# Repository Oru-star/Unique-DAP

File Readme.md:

# Unique DAP

Unique DAP is an ESP32-S3-based portable audio player built around a dedicated high-performance audio DAC and headphone amplifier. It uses a Sharp reflective memory display rather than a conventional backlit LCD, removable microSD storage, and two rotary encoders for navigation. Charging is provided through a USB Type-C port.

## Project at a glance

- **Controller:** Espressif ESP32-S3 module
- **Audio:** ESS ES9038Q2M DAC and MAX97220A headphone amplifier
- **Display:** Sharp LS032B7DD02, 3.16-inch reflective memory LCD
- **Storage:** Removable microSDXC card; 128 GB target capacity
- **Controls:** Two rotary encoders and tactile/slide controls (final switch variants still under verification)
- **Design files:** KiCad schematic and PCB, Gerbers, and printable enclosure parts

## Repository contents

| Resource | Description |
|---|---|
| [KiCad PCB](<DAP'S PCB/DAP'S PCB.kicad_pcb>) | Main board layout |
| [KiCad schematic](<DAP'S PCB/DAP'S PCB.kicad_sch>) | Main circuit schematic |
| [Gerber files](<DAP'S PCB/Gerbers/>) | PCB manufacturing outputs |
| [Printable enclosure parts](<steps/Stl for prints/>) | 3D-printable enclosure parts |
| [Full BOM with INR/USD prices and links](./Bom.csv) | Complete component register with supplier links, manufacturer references, price class and engineering notes |

## Project images

### Enclosure

<p align="center"><em>Top view</em></p>

<p align="center"><em>Front side view</em></p>

### PCB

<p align="center"><em>PCB top view</em></p>

<p align="center"><em>PCB side view</em></p>

## Bill of materials

**The complete BOM is [`Bom.csv`](./Bom.csv).** It includes all 38 BOM entries, MPNs/candidates, manufacturer references, purchase links, INR/USD unit prices, extended prices, price classification and engineering notes.

- **BOM lines with numeric prices or budget allowances:** 38 of 38
- **Budgetary estimates (not supplier quotes):** 4
- **Lines still requiring a quote:** 0
- **Current priced/estimated subtotal:** ₹12,892.44 / $137.32
- **FX reference:** 1 USD = ₹93.8516

> **Pricing caveat:** The subtotal includes supplier/list-price references and clearly marked budgetary estimates. It is not a final landed cost. Reconfirm all prices, stock, taxes, shipping, customs and reeling fees at checkout. PCB fabrication, assembly, stencil and tools are excluded.

### Detailed component pricing and purchase links

Links below were refreshed. Direct manufacturer/distributor product pages are used where available; otherwise the link opens an exact-MPN supplier search. Search results do not guarantee stock or orderability.

| Category | RefDes | Qty | Manufacturer / MPN | Manufacturer reference | Purchase link | Unit INR | Unit USD | Extended INR | Extended USD | Price class | Design status |
|---|---|---:|---|---|---|---:|---:|---:|---:|---|---|
| Display | DISP1 | 1 | `LS032B7DD02` | [Manufacturer / datasheet](https://global.sharp/products/device/lineup/selection/lcd/mobile/index.html) | [Supplier / lookup](https://www.digikey.in/en/products/detail/sharp-microelectronics/LS032B7DD02/23349498) | ₹3,739.83 | $39.85 | ₹3,739.83 | $39.85 | PRICE REFERENCE — reconfirm checkout | VERIFY |
| DAC | IC1 | 1 | `ES9038Q2M` | [Manufacturer / datasheet](https://www.mouser.in/en/ProductDetail/ESS-Technology/ES9038Q2M?qs=sPbYRqrBIVmdeUedURuuOw%3D%3D) | [Supplier / lookup](https://www.mouser.in/en/ProductDetail/ESS-Technology/ES9038Q2M?qs=sPbYRqrBIVmdeUedURuuOw%3D%3D) | ₹1,967.96 | $20.97 | ₹1,967.96 | $20.97 | PRICE REFERENCE — reconfirm checkout | BUY |
| Power IC | U1 | 1 | `TPS61023DRLR` | [Manufacturer / datasheet](https://www.ti.com/product/TPS61023/part-details/TPS61023DRLR) | [Supplier / lookup](https://www.digikey.in/en/products/detail/texas-instruments/TPS61023DRLR/11310667) | ₹116.56 | $1.24 | ₹116.56 | $1.24 | PRICE REFERENCE — reconfirm checkout | BUY |
| Power IC | U2 | 1 | `TPS63021DSJR` | [Manufacturer / datasheet](https://www.ti.com/product/TPS63021/part-details/TPS63021DSJR) | [Supplier / lookup](https://www.digikey.in/en/products/detail/texas-instruments/TPS63021DSJR/2271632) | ₹384.11 | $4.09 | ₹384.11 | $4.09 | PRICE REFERENCE — reconfirm checkout | BUY |
| Charger IC | U3 | 1 | `BQ25895RTWR` | [Manufacturer / datasheet](https://www.ti.com/product/BQ25895) | [Supplier / lookup](https://www.digikey.in/en/products/detail/texas-instruments/BQ25895RTWR/5214018) | ₹321.05 | $3.42 | ₹321.05 | $3.42 | PRICE REFERENCE — reconfirm checkout | VERIFY |
| USB-C controller | U4 | 1 | `TUSB320LAIRWBR` | [Manufacturer / datasheet](https://www.ti.com/product/TUSB320LAI/part-details/TUSB320LAIRWBR) | [Supplier / lookup](https://www.digikey.in/en/products/detail/texas-instruments/TUSB320LAIRWBR/5722618) | ₹174.05 | $1.85 | ₹174.05 | $1.85 | PRICE REFERENCE — reconfirm checkout | BUY |
| Headphone amplifier | U5 | 1 | `MAX97220AETE+T` | [Manufacturer / datasheet](https://www.analog.com/en/products/max97220a.html) | [Supplier / lookup](https://www.digikey.in/en/products/detail/analog-devices-inc-maxim-integrated/MAX97220AETE-T/2744332) | ₹245.56 | $2.62 | ₹245.56 | $2.62 | PRICE REFERENCE — reconfirm checkout | BUY |
| MCU module | U6 | 1 | `ESP32-S3-WROOM-1-N8R8` | [Manufacturer / datasheet](https://www.espressif.com/en/products/modules/esp32-s3-wroom-1) | [Supplier / lookup](https://www.digikey.in/en/products/detail/espressif-systems/ESP32-S3-WROOM-1-N8R8/16705630) | ₹603.88 | $6.43 | ₹603.88 | $6.43 | PRICE REFERENCE — reconfirm checkout | VERIFY |
| USB-C receptacle | J1 | 1 | `USB4105-GF-A` | [Manufacturer / datasheet](https://gct.co/connector/usb4105) | [Supplier / lookup](https://www.digikey.in/en/products/detail/gct/USB4105-GF-A/11198510) | ₹76.44 | $0.81 | ₹76.44 | $0.81 | PRICE REFERENCE — reconfirm checkout | VERIFY |
| Battery header | J2 | 1 | `TSW-102-07-G-S` | [Manufacturer / datasheet](https://www.samtec.com/products/tsw-102-07-g-s) | [Supplier / lookup](https://www.digikey.in/en/products/detail/samtec-inc/TSW-102-07-G-S/1101325) | ₹20.07 | $0.21 | ₹20.07 | $0.21 | PRICE REFERENCE — reconfirm checkout | VERIFY |
| Programming header | J3 | 1 | `TSW-105-07-G-S` | [Manufacturer / datasheet](https://www.samtec.com/products/tsw-105-07-g-s) | [Supplier / lookup](https://www.digikey.in/en/products/detail/samtec-inc/TSW-105-07-G-S/1101322) | ₹40.66 | $0.43 | ₹40.66 | $0.43 | PRICE REFERENCE — reconfirm checkout | BUY |
| Display FPC connector | J4 | 1 | `FH34SRJ-10S-0.5SH(50)` | [Manufacturer / datasheet](https://www.hirose.com/en/product/p/CL0580-1251-5-50) | [Supplier / lookup](https://www.digikey.in/en/products/detail/hirose-electric-co-ltd/FH34SRJ-10S-0-5SH-50/3880296) | ₹116.57 | $1.24 | ₹116.57 | $1.24 | PRICE REFERENCE — reconfirm checkout | VERIFY |
| Headphone jack | J5 | 1 | `SJ1-3533NG` | [Manufacturer / datasheet](https://www.digikey.in/en/products/detail/same-sky-formerly-cui-devices/SJ1-3533NG/738701) | [Supplier / lookup](https://www.digikey.in/en/products/detail/same-sky-formerly-cui-devices/SJ1-3533NG/738701) | ₹160.74 | $1.71 | ₹160.74 | $1.71 | PRICE REFERENCE — reconfirm checkout | BUY |
| Ferrite bead | FB1 | 1 | `BLM21PG601SN1D` | [Manufacturer / datasheet](https://www.murata.com/en-global/products/productdetail?partno=BLM21PG601SN1D) | [Supplier / lookup](https://www.digikey.in/en/products/detail/murata-electronics/BLM21PG601SN1D/24763118) | ₹11.47 | $0.12 | ₹11.47 | $0.12 | PRICE REFERENCE — reconfirm checkout | VERIFY |
| Power inductor | L1 | 1 | `74438357010` | [Manufacturer / datasheet](https://www.we-online.com/en/components/products/WE-MAPI) | [Supplier / lookup](https://in.element14.com/wurth-elektronik/74438357010/inductor-1uh-7-4a-20-shielded/dp/2842181) | ₹161.46 | $1.72 | ₹161.46 | $1.72 | PRICE REFERENCE — reconfirm checkout | HOLD |
| Power inductor | L2 | 1 | `XFL4020-152ME` | [Manufacturer / datasheet](https://www.coilcraft.com/en-us/products/power/high-voltage-inductors/xfl/xfl4020/) | [Supplier / lookup](https://www.coilcraft.com/en-us/products/power/high-voltage-inductors/xfl/xfl4020/) | ₹231.81 | $2.47 | ₹231.81 | $2.47 | LIST PRICE REFERENCE — confirm configuration | HOLD |
| Power inductor | L3 | 1 | `DFE322512F-2R2M=P2` | [Manufacturer / datasheet](https://www.murata.com/en-global/products/productdetail?partno=DFE322512F-2R2M%3DP2) | [Supplier / lookup](https://www.digikey.in/en/products/detail/murata-electronics/DFE322512F-2R2M-P2/9815914) | ₹46.82 | $0.50 | ₹46.82 | $0.50 | PRICE REFERENCE — reconfirm checkout | HOLD |
| Oscillator | Y1 | 1 | `ASE-40.000MHZ-L-C-T` | [Manufacturer / datasheet](https://abracon.com/Oscillators/ASE.pdf) | [Supplier / lookup](https://www.digikey.in/en/products/detail/abracon-llc/ASE-40-000MHZ-L-C-T/5980161) | ₹99.37 | $1.06 | ₹99.37 | $1.06 | PRICE REFERENCE — reconfirm checkout | VERIFY |
| Capacitor | C1,C8-C10,C13,C14,C30 | 7 | `CL10A106KP8NNND` | [Manufacturer / datasheet](https://www.samsungsem.com/global/product/passive-component/mlcc.do) | [Supplier / lookup](https://www.digikey.in/en/products/detail/samsung-electro-mechanics/CL10A106KP8NNND/3894249) | ₹19.11 | $0.20 | ₹133.77 | $1.43 | PRICE REFERENCE — reconfirm checkout | VERIFY |
| Capacitor | C2,C16-C21,C23,C28,C31 | 10 | `GRM188R71H104KA93D` | [Manufacturer / datasheet](https://www.murata.com/en-global/products/productdetail?partno=GRM188R71H104KA93D) | [Supplier / lookup](https://www.digikey.in/en/products/detail/murata-electronics/GRM188R71H104KA93D/587143) | ₹15.29 | $0.16 | ₹152.90 | $1.63 | PRICE REFERENCE — reconfirm checkout | VERIFY |
| Capacitor | C3-C6 | 4 | `CC0603MRX5R5BB226` | [Manufacturer / datasheet](https://www.yageo.com/en/ProductSearch/Index) | [Supplier / lookup](https://www.digikey.in/en/products/detail/yageo/CC0603MRX5R5BB226/5195222) | ₹54.46 | $0.58 | ₹217.84 | $2.32 | PRICE REFERENCE — reconfirm checkout | HOLD |
| Capacitor | C7,C12,C24-C27,C29,C32,C34,C35 | 10 | `C1608X7R1C105K080AC` | [Manufacturer / datasheet](https://product.tdk.com/en/search/capacitor/ceramic/mlcc/info?part_no=C1608X7R1C105K080AC) | [Supplier / lookup](https://www.digikey.in/en/products/result?keywords=C1608X7R1C105K080AC) | ₹11.47 | $0.12 | ₹114.70 | $1.22 | PRICE REFERENCE — reconfirm checkout | VERIFY |
| Capacitor | C15,C22,C36-C39 | 6 | `GRM188R71A475KE15D` | [Manufacturer / datasheet](https://www.murata.com/en-global/products/productdetail?partno=GRM188R71A475KE15D) | [Supplier / lookup](https://www.digikey.in/en/products/result?keywords=GRM188R71A475KE15D) | ₹5.00 | $0.05 | ₹30.00 | $0.32 | ESTIMATE — not a supplier quote | VERIFY |
| Capacitor | C11 | 1 | `GRM188R71E473KA61D` | [Manufacturer / datasheet](https://www.murata.com/en-global/products/productdetail?partno=GRM188R71E473KA61D) | [Supplier / lookup](https://www.digikey.in/en/products/result?keywords=GRM188R71E473KA61D) | ₹3.00 | $0.03 | ₹3.00 | $0.03 | ESTIMATE — not a supplier quote | VERIFY |
| Capacitor | C33 | 1 | `GRM1885C1H561JA01D` | [Manufacturer / datasheet](https://www.murata.com/en-global/products/productdetail?partno=GRM1885C1H561JA01D) | [Supplier / lookup](https://www.digikey.in/en/products/detail/murata-electronics/GRM1885C1H561JA01D/586954) | ₹15.29 | $0.16 | ₹15.29 | $0.16 | PRICE REFERENCE — reconfirm checkout | VERIFY |
| Resistor | R4,R6,R7,R9-R11,R15,R16,R18,R19,R27 | 11 | `RC0805FR-0710KL` | [Manufacturer / datasheet](https://www.yageo.com/en/ProductSearch/Index) | [Supplier / lookup](https://www.digikey.in/en/products/detail/yageo/RC0805FR-0710KL/730482) | ₹3.25 | $0.03 | ₹35.74 | $0.38 | PRICE REFERENCE — reconfirm checkout | BUY |
| Resistor | R17,R20-R26 | 8 | `CRG0805F20K` | [Manufacturer / datasheet](https://www.te.com/en/product-1622825-1.html) | [Supplier / lookup](https://www.digikey.in/en/products/detail/te-connectivity-passive-product/CRG0805F20K/2380867) | ₹9.51 | $0.10 | ₹76.08 | $0.81 | PRICE REFERENCE — reconfirm checkout | BUY |
| Resistor | R5,R8 | 2 | `RC0805FR-07260RL` | [Manufacturer / datasheet](https://www.yageo.com/en/ProductSearch/Index) | [Supplier / lookup](https://www.digikey.in/en/products/result?keywords=RC0805FR-07260RL) | ₹3.00 | $0.03 | ₹6.00 | $0.06 | ESTIMATE — not a supplier quote | VERIFY |
| Resistor | R13,R14 | 2 | `RC0805FR-074K7L` | [Manufacturer / datasheet](https://www.yageo.com/en/ProductSearch/Index) | [Supplier / lookup](https://www.digikey.in/en/products/detail/yageo/RC0805FR-074K7L/727929) | ₹9.56 | $0.10 | ₹19.12 | $0.20 | PRICE REFERENCE — reconfirm checkout | VERIFY |
| Resistor | R1 | 1 | `RC0805FR-07100KL` | [Manufacturer / datasheet](https://www.yageo.com/en/ProductSearch/Index) | [Supplier / lookup](https://www.digikey.in/en/products/detail/yageo/RC0805FR-07100KL/730491) | ₹10.51 | $0.11 | ₹10.51 | $0.11 | PRICE REFERENCE — reconfirm checkout | VERIFY |
| Resistor | R2 | 1 | `RC0805FR-0727K4L` | [Manufacturer / datasheet](https://www.yageo.com/en/ProductSearch/Index) | [Supplier / lookup](https://www.digikey.in/en/products/detail/yageo/RC0805FR-0727K4L/727782) | ₹9.56 | $0.10 | ₹9.56 | $0.10 | PRICE REFERENCE — reconfirm checkout | VERIFY |
| Resistor | R3 | 1 | `RC0805FR-07200KL` | [Manufacturer / datasheet](https://www.yageo.com/en/ProductSearch/Index) | [Supplier / lookup](https://www.digikey.in/en/products/detail/yageo/RC0805FR-07200KL/730671) | ₹9.56 | $0.10 | ₹9.56 | $0.10 | PRICE REFERENCE — reconfirm checkout | VERIFY |
| Resistor | R12 | 1 | `RC0805FR-07900KL` | [Manufacturer / datasheet](https://www.yageo.com/en/ProductSearch/Index) | [Supplier / lookup](https://www.digikey.in/en/products/result?keywords=RC0805FR-07900KL) | ₹3.00 | $0.03 | ₹3.00 | $0.03 | ESTIMATE — not a supplier quote | VERIFY |
| Rotary encoder | SW2,SW3 | 2 | `EC11E family — EC11E15204A3 price candidate` | [Manufacturer / datasheet](https://tech.alpsalpine.com/e/products/category/enc/) | [Supplier / lookup](https://www.digikey.in/en/products/detail/alps-alpine/EC11E15204A3/21721644) | ₹421.38 | $4.49 | ₹842.76 | $8.98 | PRICE REFERENCE — reconfirm checkout | HOLD |
| Slide / push controls | SW1,SW2-BOOT1,SW4-SW6 | 5 | `CHS-01A` | [Manufacturer / datasheet](https://www.nidec.com/en/product/search/category/B102/M101/S100/) | [Supplier / lookup](https://www.tanotis.com/products/nidec-copal-electronics-chs-01a-dip-switch-1pos-spst-slide-smd) | ₹169.20 | $1.80 | ₹846.00 | $9.01 | PRICE REFERENCE — reconfirm checkout | HOLD |
| Battery (off-board) | BAT1 (not a PCB footprint) | 1 | `WLY104050 — exact supplier/lead configuration TBD` | [Manufacturer / datasheet](https://robu.in/product-category/single-cell-micro-lipo-battery/) | [Supplier / lookup](https://robu.in/product-category/single-cell-micro-lipo-battery/) | ₹600.00 | $6.39 | ₹600.00 | $6.39 | INDIA LISTING — reconfirm checkout | HOLD |
| microSD card socket | J6 | 1 | `DM3AT-SF-PEJM5` | [Manufacturer / datasheet](https://www.hirose.com/product/document?clcode=CL0609-0031-0-00&documenttype=Drawing&lang=en) | [Supplier / lookup](https://www.digikey.in/en/products/detail/hirose-electric-co-ltd/DM3AT-SF-PEJM5/2533565) | ₹339.20 | $3.61 | ₹339.20 | $3.61 | PRICE REFERENCE — reconfirm checkout | VERIFY |
| Storage media | SD1 (off-board) | 1 | `SDSQUAB-128G-GN6MN` | [Manufacturer / datasheet](https://www.westerndigital.com/products/memory-cards/sandisk-ultra-uhs-i-microsd) | [Supplier / lookup](https://indiastore-stage.westerndigital.com/store/sdsquab-128g-gn6mn.html) | ₹909.00 | $9.69 | ₹909.00 | $9.69 | PRICE REFERENCE — reconfirm checkout | VERIFY |

### Link verification note

Direct DigiKey and Mouser product pages were substituted for several generic or stale search links. For parts without a confirmed exact product page, the purchase link opens a supplier search for the exact MPN; verify the result and suffix before ordering.

## Engineering review — unresolved approvals

**A numeric price, supplier link or footprint match does not constitute engineering approval.** The following checks remain mandatory before fabrication:

- **Power inductors L1/L2/L3:** Match each inductor to the actual converter topology, switching frequency, inductance range, peak and RMS current, saturation criterion, DCR loss, thermal rise, footprint and layout. For L2, the Coilcraft XFL4020 1.5 µH series data gives 15.8 mΩ maximum DCR, 4.1 A Isat at 10% inductance drop and 6.7 A Irms at 20°C rise. Compare against the calculated worst-case peak current, not just the converter's headline output current.
- **Battery BAT1:** Robu lists WLY104050 3.7 V, 2500 mAh at ₹600. This is a price reference only. Obtain the cell datasheet and verify dimensions, protection PCM, maximum charge voltage/current, continuous discharge current, NTC/temperature-sense requirements, lead connector and polarity. Keep HOLD until these are confirmed.
- **Battery connector J2:** Samtec TSW-102 is an unpolarized header. Prefer a keyed, locking connector matched to the battery harness; verify polarity and contact current. Do not approve an unkeyed battery connector without a deliberate safety review.
- **Capacitors C15,C22,C36-C39:** The ₹5/pc allowance for the 4.7 µF Murata candidate is a budget estimate, not a quote. Verify exact MPN and lifecycle, voltage rating, dielectric and effective capacitance at the actual DC bias.
- **Capacitor C11:** The ₹3/pc allowance for the 47 nF candidate is a budget estimate. Verify exact MPN, voltage rating, dielectric, tolerance and package against the circuit requirement.
- **Resistors R5/R8:** The ₹3/pc allowance is a budget estimate. Exact Yageo MPN RC0805FR-07260RL was not confirmed in distributor search. Verify the intended 260 Ω value and exact orderable code.
- **Resistor R12:** The ₹3/pc allowance is a budget estimate. Exact Yageo MPN RC0805FR-07900KL was not confirmed. Verify that 900 kΩ is intentional and confirm the exact orderable code; do not silently change it to 909 kΩ or 910 kΩ.
- **Oscillator Y1:** Confirm the 40 MHz oscillator against ES9038Q2M MCLK requirements and the full 44.1 kHz / 48 kHz audio clock plan before ordering.
- **Rotary encoders SW2/SW3:** EC11E15204A3 is a candidate without a push switch. Select a correct push-switch variant or add separate tact switches.
- **Control switches:** Copal CHS-01A is a slide switch, not a momentary pushbutton. Resolve symbol, footprint and actual user-interface function.
- **Capacitors C3-C6:** 22 µF, 6.3 V, 0603 MLCCs need effective-capacitance/DC-bias derating checks, especially on a 5 V rail.
- **Capacitor C2 group:** Confirm lifecycle status of the proposed 100 nF Murata part and choose an active replacement if obsolete.
- **Display DISP1:** Verify Sharp LS032B7DD02 full power rails, logic levels, FPC pinout, flex thickness and contact orientation against the exact panel documentation.
- **microSD J6:** Verify Hirose DM3AT-SF-PEJM5 pad mapping, shield pads and mechanical dimensions against the manufacturer drawing. Card-detect contacts may remain unconnected if unused.
- **USB-C J1:** Verify receptacle footprint, shell stakes, CC configuration, VBUS path, ESD protection and port role against the intended charge/data architecture.

## Assembly and bring-up

1. **Prepare parts:** Check exact MPN, package, footprint, pinout, ratings, lifecycle and availability. Do not substitute solely on nominal value.
2. **Review fabrication outputs:** Inspect the schematic, PCB, design-rule results, drill files, copper, solder mask, silkscreen and board outline. Independently inspect Gerbers before ordering.
3. **Inspect the bare PCB:** Check board damage, opens, shorts, solder-mask defects, drill sizes and connector alignment.
4. **Populate the PCB:** Use the assembly drawing and BOM. Apply solder paste with a stencil, place SMD parts, reflow to an appropriate profile, then install through-hole parts. Inspect fine-pitch ICs and connectors under magnification.
5. **Unpowered checks:** Measure resistance from every power rail to ground, verify polarity, inspect for solder bridges and confirm connector pin mapping.
6. **First power-up:** Use a current-limited bench supply rather than the Li-Po battery. Verify regulator outputs, startup sequencing, ripple, current draw and thermal behaviour before connecting the battery.
7. **Install display:** Confirm Sharp LS032B7DD02 flex orientation, pinout and supply rails. Never hot-plug the FPC.
8. **Install storage:** Use a compatible 128 GB microSDXC card. Firmware must support the selected filesystem; many 128 GB cards ship exFAT-formatted.
9. **Connect battery:** Only after battery polarity, protection, charger configuration, charge current and temperature sensing are verified against the cell datasheet.
10. **Functional validation:** Test display refresh, encoder direction/debounce, buttons, microSD read/write, USB-C operation, audio sample rates, headphone output and thermal performance.

## Firmware and storage notes

- The ESP32-S3 firmware must initialize the display, controls, microSD interface, audio pipeline, DAC and headphone amplifier.
- A 128 GB microSDXC card is commonly supplied as exFAT. Firmware must include compatible filesystem support or a documented reformat procedure.
- The microSD card is removable music/data storage; do not claim it is pre-flashed with firmware unless a specific image and flashing procedure are supplied. ESP32-S3 boot firmware normally resides in module flash.

## Project status

This is an actively developed hardware project. Prices and links are procurement references, not guarantees of stock, compatibility or production readiness. Electrical performance, power integrity, audio performance, thermal behaviour and enclosure fit require validation on the assembled hardware.

**Fabrication status: NOT APPROVED by this README/BOM alone.** Resolve all HOLD/VERIFY items, complete schematic and PCB review, and validate the Gerbers before ordering.

## License

Add the project license and any required third-party hardware/documentation attribution.

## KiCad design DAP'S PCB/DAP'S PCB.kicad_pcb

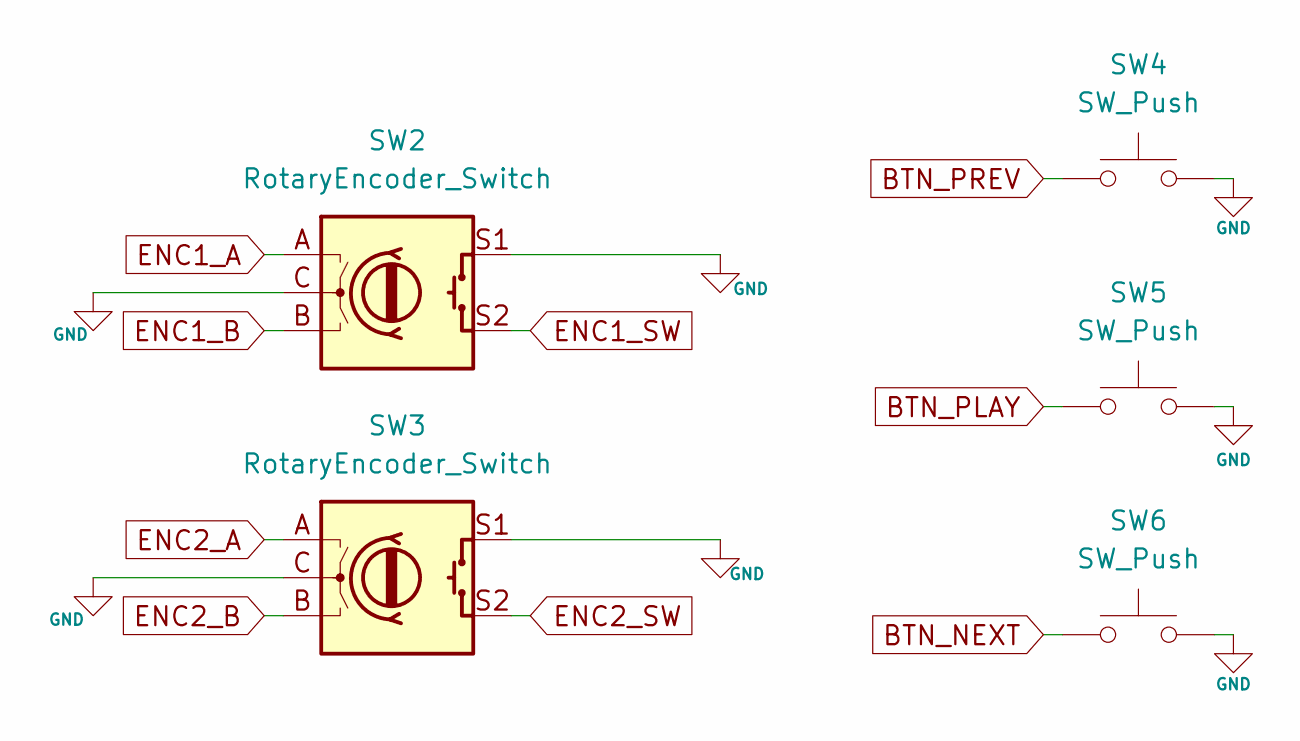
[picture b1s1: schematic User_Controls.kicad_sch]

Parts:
SW2, SW3: RotaryEncoder_Switch; RotaryEncoder_Alps_EC11E-Switch_Vertical_H20mm
SW4, SW5, SW6: SW_Push; SW_DIP_SPSTx01_Slide_Copal_CHS-01A_W5.08mm_P1.27mm_JPin

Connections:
BTN_NEXT: SW6.1; also elsewhere on the board
BTN_PLAY: SW5.1; also elsewhere on the board
BTN_PREV: SW4.1; also elsewhere on the board
DAC_DGND: SW2.C, SW2.S1, SW3.C, SW3.S1, SW4.2, SW5.2, SW6.2; also elsewhere on the board
ENC1_A: SW2.A; also elsewhere on the board
ENC1_B: SW2.B; also elsewhere on the board
ENC1_SW: SW2.S2; also elsewhere on the board
ENC2_A: SW3.A; also elsewhere on the board
ENC2_B: SW3.B; also elsewhere on the board
ENC2_SW: SW3.S2; also elsewhere on the board

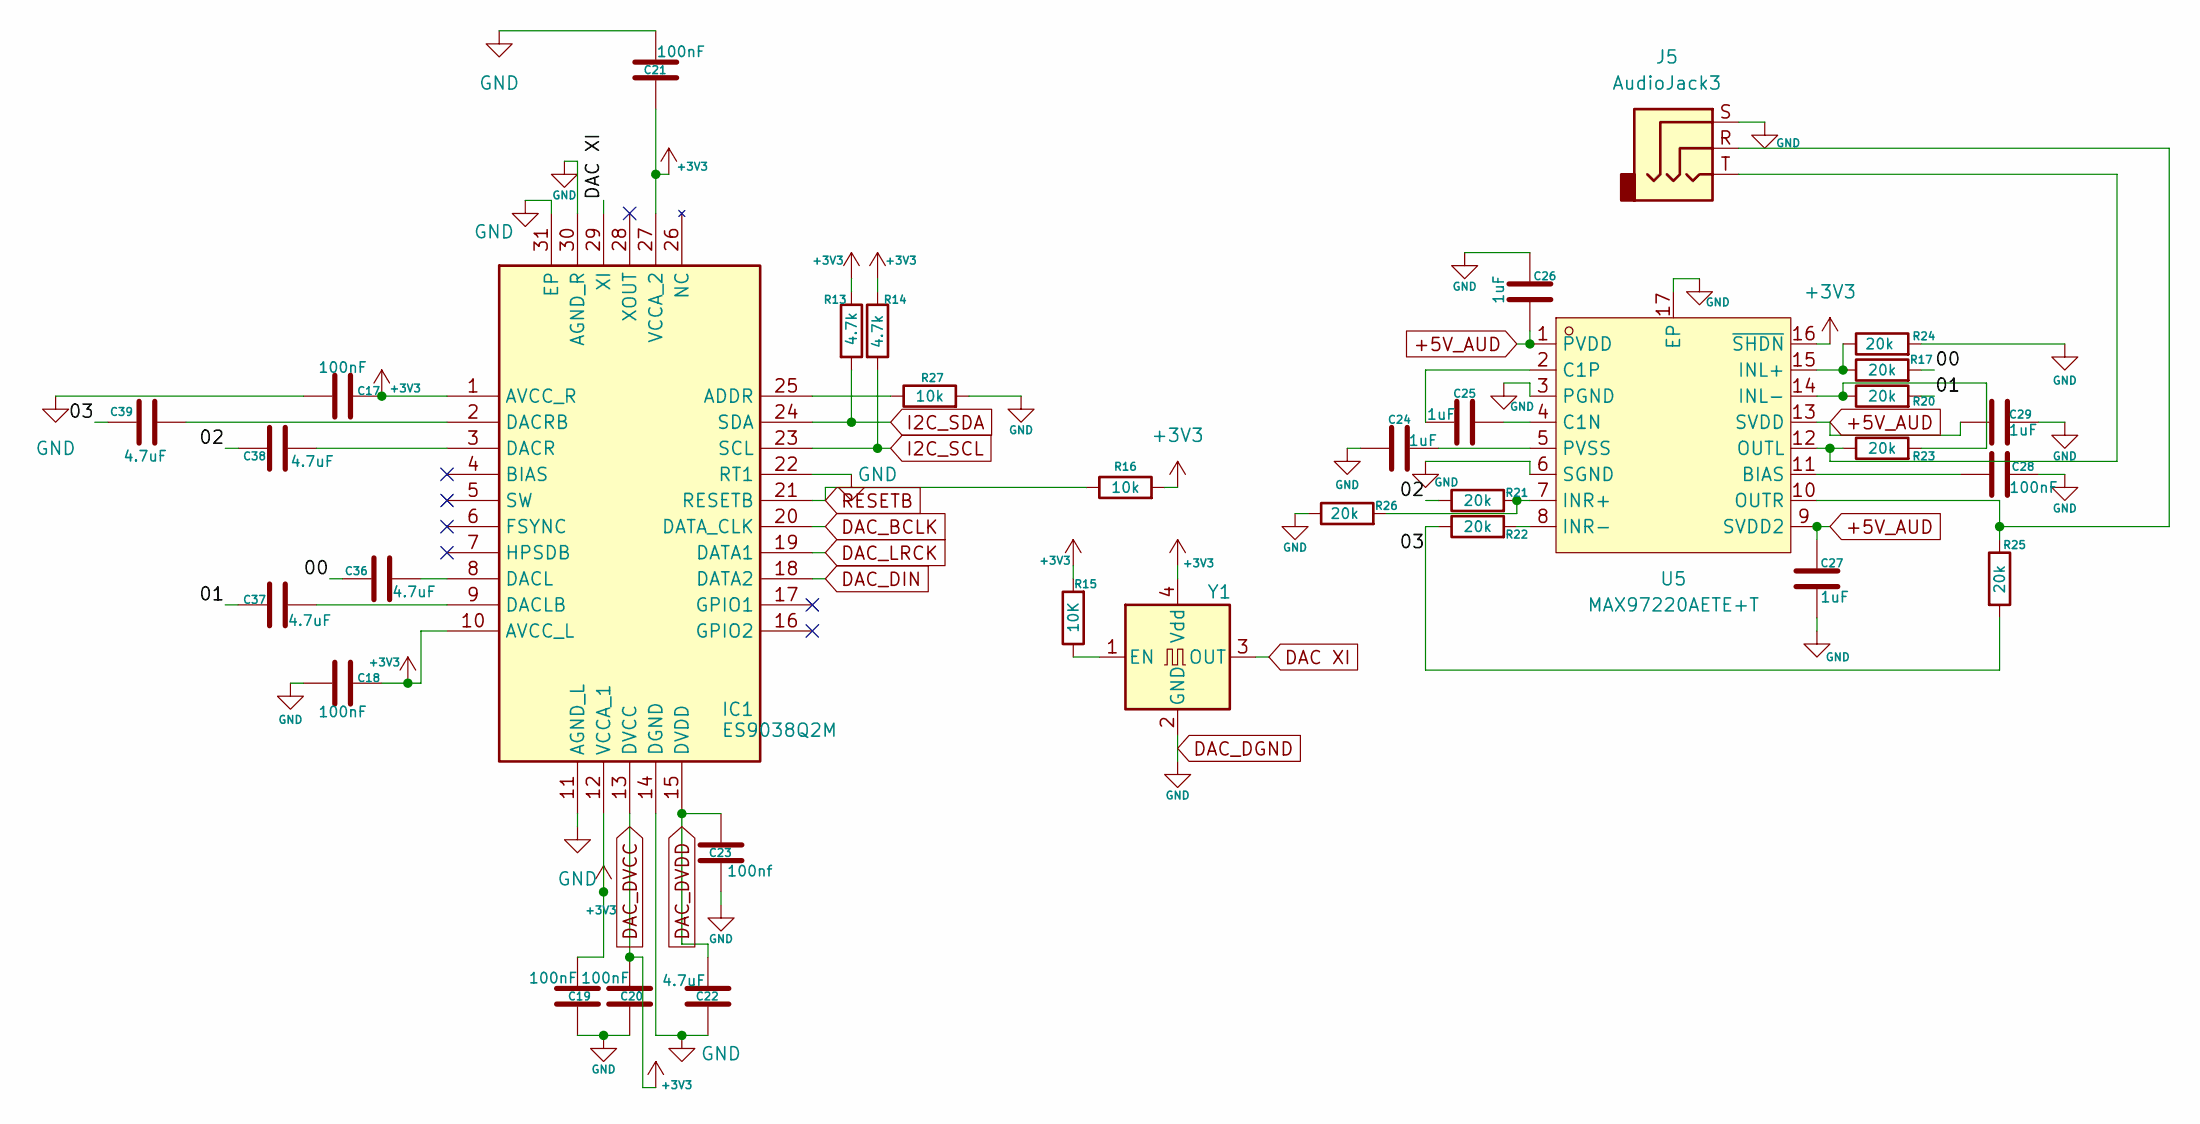
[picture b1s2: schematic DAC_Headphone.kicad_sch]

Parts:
C17, C18, C19, C20, C21, C28: 100nF; C_0603_1608Metric
C22, C36, C37, C38, C39: 4.7uF; C_0603_1608Metric
C23: 100nf; C_0603_1608Metric
C24, C25, C26, C27, C29: 1uF; C_0603_1608Metric
IC1: ES9038Q2M; QFN40P300X500X80-31N-D; Manufacturer_Part_Number ES9038Q2M; Mouser Part Number 460-ES9038Q2M
J5: AudioJack3; Jack_3.5mm_CUI_SJ1-3533NG_Horizontal
R13, R14: 4.7k; R_0805_2012Metric
R15: 10K; R_0805_2012Metric
R16, R27: 10k; R_0805_2012Metric
R17, R20, R21, R22, R23, R24, R25, R26: 20k; R_0805_2012Metric
U5: MAX97220AETE+T; QFN-16_L3.0-W3.0-P0.50-BL-EP1.5; MPN MAX97220AETE+T; LCSC Part C2682711
Y1: 40 MHz; Oscillator_SMD_Abracon_ASE-4Pin_3.2x2.5mm

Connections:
+5V_AUD: C26.2, C27.1, C29.1, U5.1 (PVDD), U5.9 (SVDD2), U5.13 (SVDD); also elsewhere on the board
/DAC_Headphone/00: C36.1, R17.2
/DAC_Headphone/01: C37.1, R20.2
/DAC_Headphone/02: C38.1, R21.1
/DAC_Headphone/03: C39.1, R22.1, R25.2
DAC XI: IC1.29 (XI), Y1.3 (OUT)
DAC_BCLK: IC1.20 (DATA_CLK); also elsewhere on the board
DAC_DGND: C17.2, C18.1, C19.2, C20.2, C21.1, C22.2, C23.2, C24.1, C26.1, C27.2, C28.2, C29.2, IC1.11 (AGND_L), IC1.14 (DGND), IC1.22 (RT1), IC1.30 (AGND_R), IC1.31 (EP), J5.S, R24.2, R26.1, R27.2, U5.3 (PGND), U5.6 (SGND), U5.17 (EP), Y1.2 (GND); also elsewhere on the board
DAC_DIN: IC1.18 (DATA2); also elsewhere on the board
DAC_DVCC: C17.1, C18.2, C19.1, C20.1, C21.2, IC1.1 (AVCC_R), IC1.10 (AVCC_L), IC1.12 (VCCA_1), IC1.13 (DVCC), IC1.27 (VCCA_2), R13.1, R14.1, R15.2, R16.2, U5.16 (~SHDN), Y1.4 (Vdd); also elsewhere on the board
DAC_DVDD: C22.1, C23.1, IC1.15 (DVDD)
DAC_LRCK: IC1.19 (DATA1); also elsewhere on the board
I2C_SCL: IC1.23 (SCL), R14.2; also elsewhere on the board
I2C_SDA: IC1.24 (SDA), R13.2; also elsewhere on the board
unnamed: IC1.25 (ADDR), R27.1
unnamed: C36.2, IC1.8 (DACL)
unnamed: C37.2, IC1.9 (DACLB)
unnamed: C38.2, IC1.3 (DACR)
unnamed: C39.2, IC1.2 (DACRB)
unnamed: C28.1, U5.11 (BIAS)
unnamed: C25.2, U5.4 (C1N)
unnamed: C25.1, U5.2 (C1P)
unnamed: R17.1, R24.1, U5.15 (INL+)
unnamed: R20.1, R23.2, U5.14 (INL-)
unnamed: R21.2, R26.2, U5.7 (INR+)
unnamed: R22.2, U5.8 (INR-)
unnamed: J5.T, R23.1, U5.12 (OUTL)
unnamed: J5.R, R25.1, U5.10 (OUTR)
unnamed: C24.2, U5.5 (PVSS)
unnamed: R15.1, Y1.1 (EN)
RESETB: IC1.21 (RESETB), R16.1; also elsewhere on the board

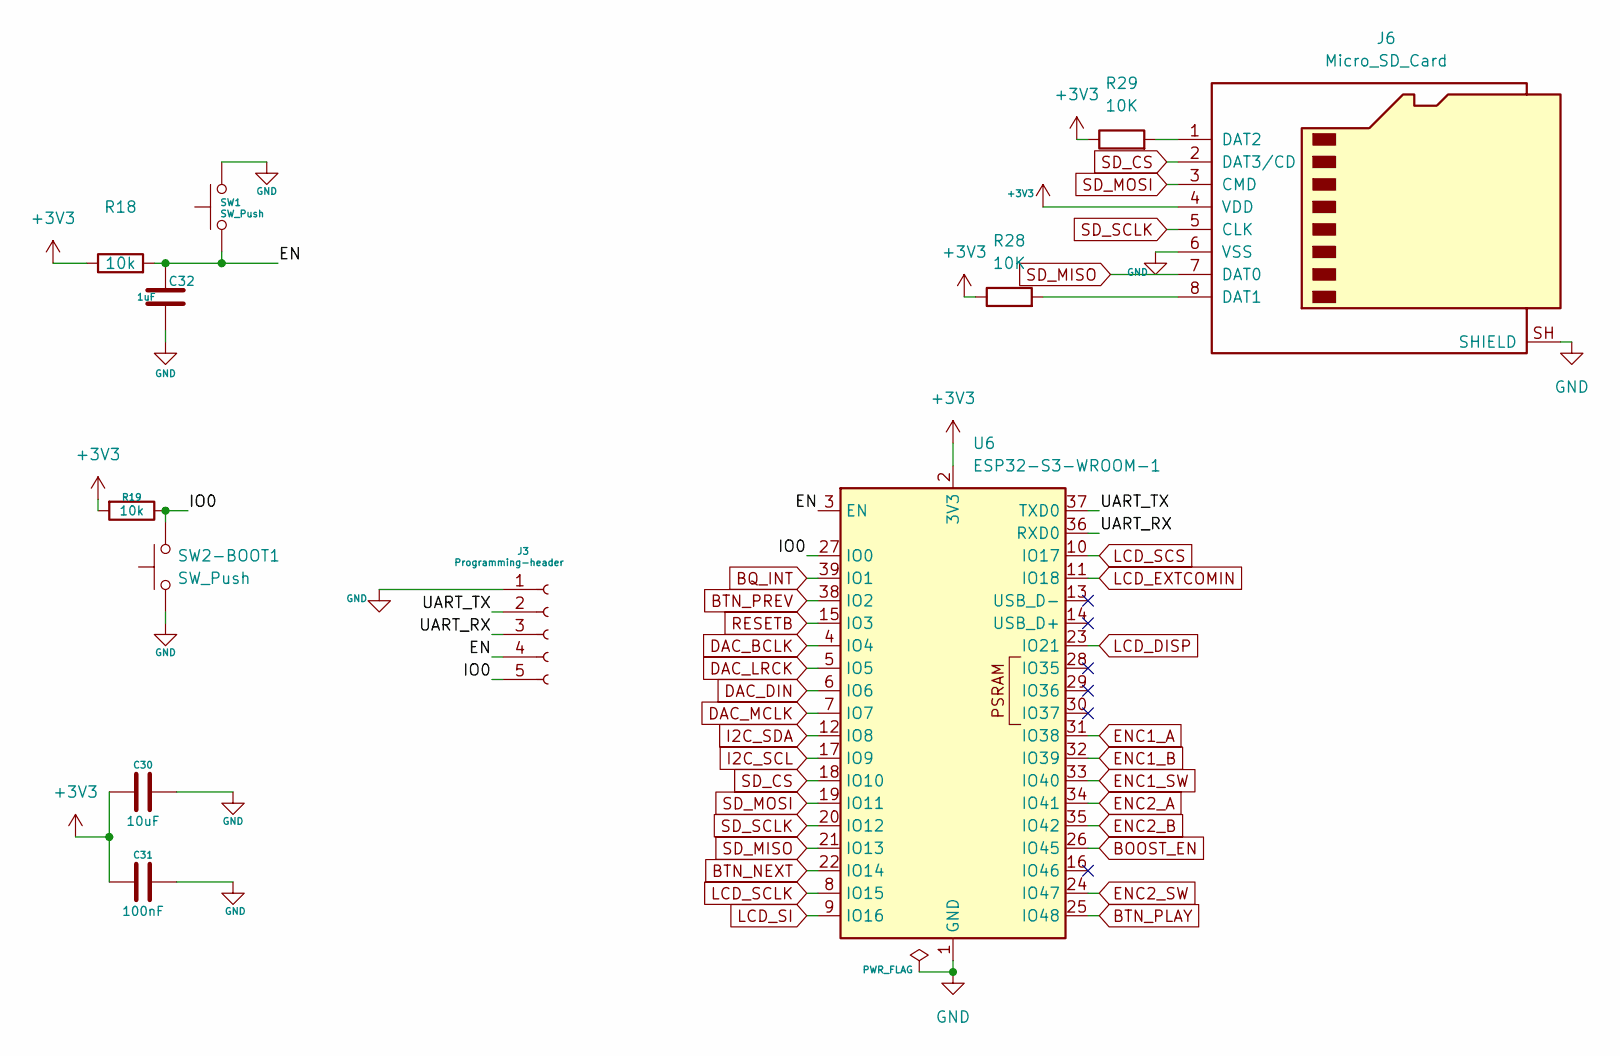
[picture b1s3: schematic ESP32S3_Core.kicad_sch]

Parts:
C30: 10uF; C_0603_1608Metric
C31: 100nF; C_0603_1608Metric
C32: 1uF; C_0603_1608Metric
J3: Programming-header; PinHeader_1x05_P2.54mm_Vertical
J6: Micro_SD_Card; microSD_HC_Hirose_DM3AT-SF-PEJM5
R18, R19: 10k; R_0805_2012Metric
R28, R29: 10K; R_0805_2012Metric
SW1, SW2-BOOT1: SW_Push; SW_DIP_SPSTx01_Slide_Copal_CHS-01A_W5.08mm_P1.27mm_JPin
U6: ESP32-S3-WROOM-1

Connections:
/ESP32S3_Core/EN: C32.2, J3.4, R18.2, SW1.1, U6.3 (EN)
/ESP32S3_Core/IO0: J3.5, R19.1, SW2-BOOT1.2, U6.27 (IO0)
/ESP32S3_Core/UART_RX: J3.3, U6.36 (RXD0)
/ESP32S3_Core/UART_TX: J3.2, U6.37 (TXD0)
BOOST_EN: U6.26 (IO45); also elsewhere on the board
BQ_INT: U6.39 (IO1); also elsewhere on the board
BTN_NEXT: U6.22 (IO14); also elsewhere on the board
BTN_PLAY: U6.25 (IO48); also elsewhere on the board
BTN_PREV: U6.38 (IO2); also elsewhere on the board
DAC_BCLK: U6.4 (IO4); also elsewhere on the board
DAC_DGND: C30.2, C31.2, C32.1, J3.1, J6.6 (VSS), J6.SH (SHIELD), SW1.2, SW2-BOOT1.1, U6.1 (GND), U6.40 (GND), U6.41 (GND); also elsewhere on the board
DAC_DIN: U6.6 (IO6); also elsewhere on the board
DAC_DVCC: C30.1, C31.1, J6.4 (VDD), R18.1, R19.2, R28.1, R29.1, U6.2 (3V3); also elsewhere on the board
DAC_LRCK: U6.5 (IO5); also elsewhere on the board
DAC_MCLK: U6.7 (IO7)
ENC1_A: U6.31 (IO38); also elsewhere on the board
ENC1_B: U6.32 (IO39); also elsewhere on the board
ENC1_SW: U6.33 (IO40); also elsewhere on the board
ENC2_A: U6.34 (IO41); also elsewhere on the board
ENC2_B: U6.35 (IO42); also elsewhere on the board
ENC2_SW: U6.24 (IO47); also elsewhere on the board
I2C_SCL: U6.17 (IO9); also elsewhere on the board
I2C_SDA: U6.12 (IO8); also elsewhere on the board
LCD_DISP: U6.23 (IO21); also elsewhere on the board
LCD_EXTCOMIN: U6.11 (IO18); also elsewhere on the board
LCD_SCLK: U6.8 (IO15); also elsewhere on the board
LCD_SCS: U6.10 (IO17); also elsewhere on the board
LCD_SI: U6.9 (IO16); also elsewhere on the board
unnamed: J6.8 (DAT1), R28.2
unnamed: J6.1 (DAT2), R29.2
RESETB: U6.15 (IO3); also elsewhere on the board
SD_CS: J6.2 (DAT3/CD), U6.18 (IO10)
SD_MISO: J6.7 (DAT0), U6.21 (IO13)
SD_MOSI: J6.3 (CMD), U6.19 (IO11)
SD_SCLK: J6.5 (CLK), U6.20 (IO12)

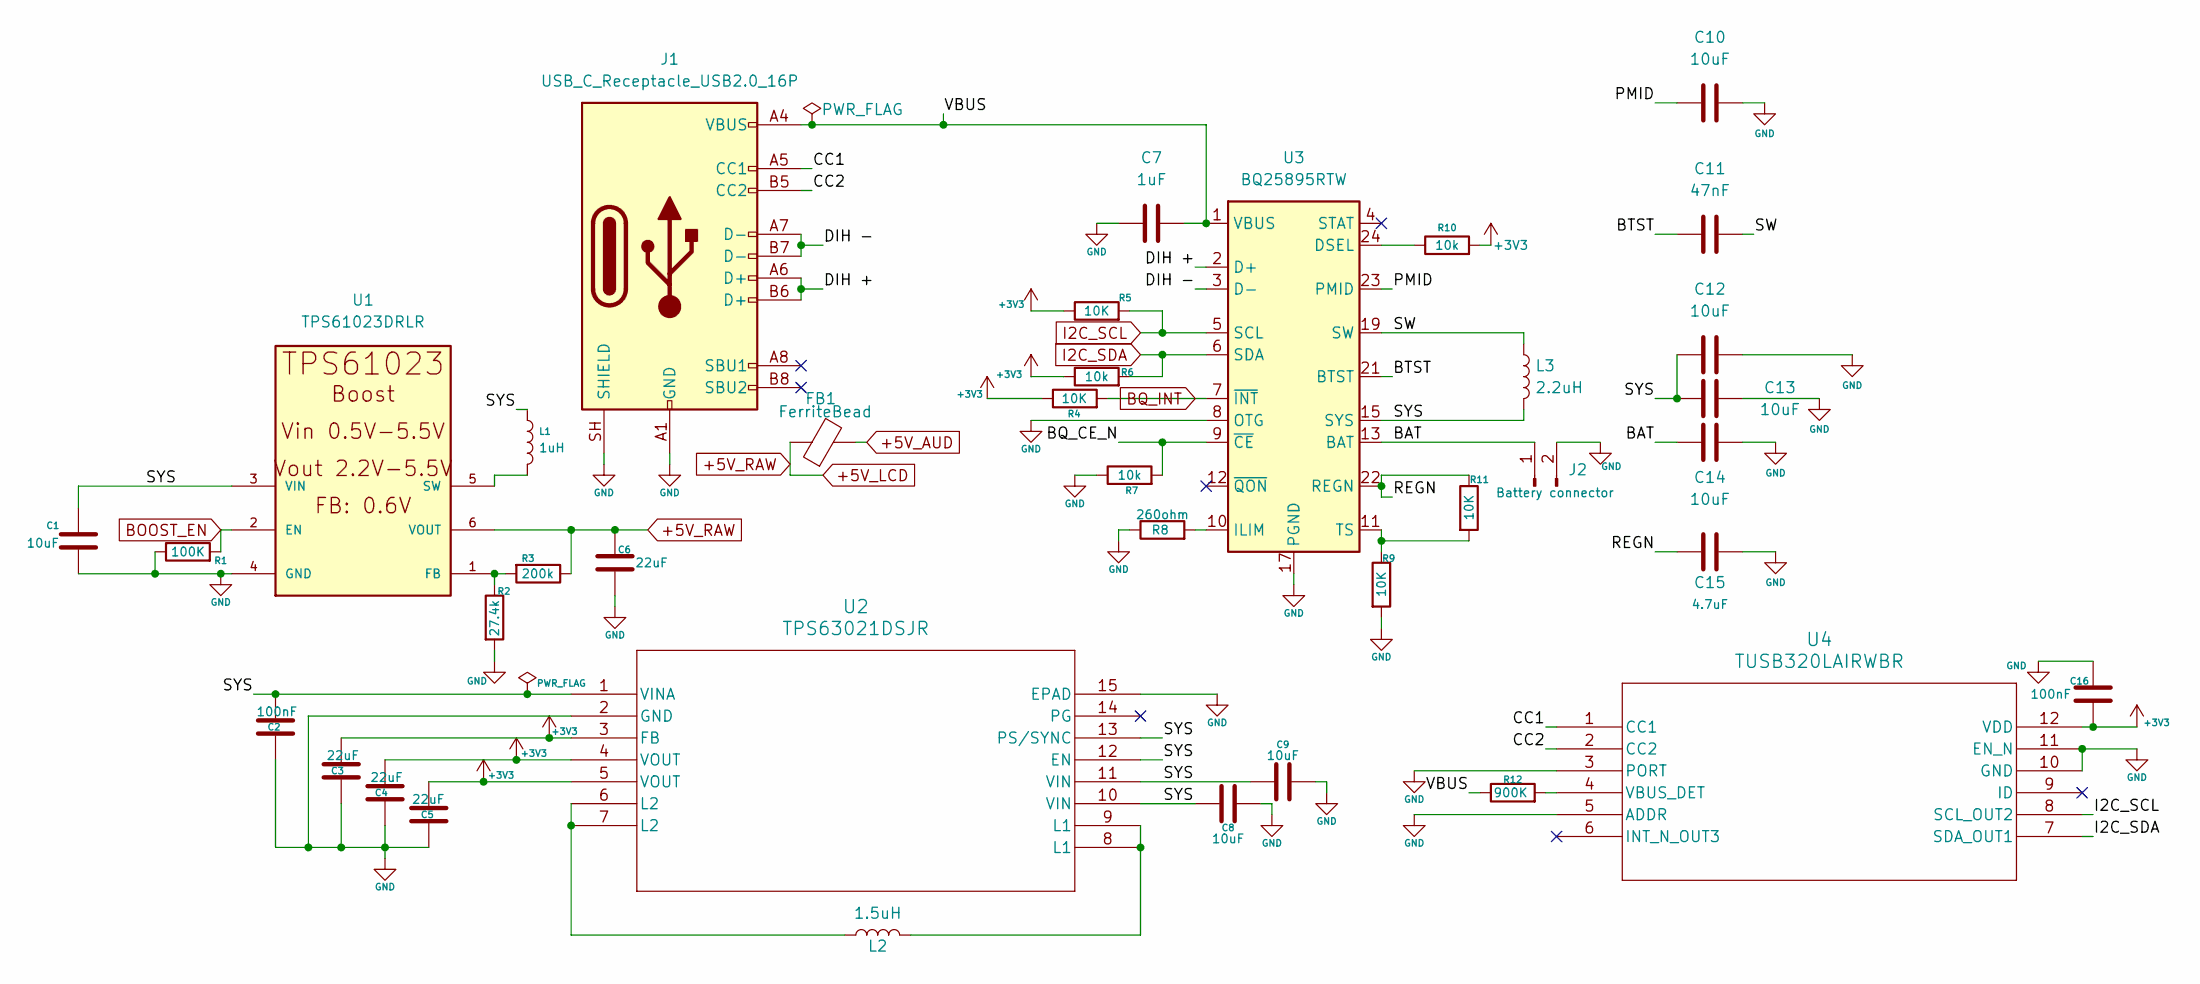
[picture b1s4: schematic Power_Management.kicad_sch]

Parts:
C1, C8, C9, C10, C12, C13, C14: 10uF; C_0603_1608Metric
C2, C16: 100nF; C_0603_1608Metric
C3, C4, C5, C6: 22uF; C_0603_1608Metric
C7: 1uF; C_0603_1608Metric
C11: 47nF; C_0603_1608Metric
C15: 4.7uF; C_0603_1608Metric
FB1: FerriteBead; L_0805_2012Metric
J1: USB_C_Receptacle_USB2.0_16P; USB_C_Receptacle_GCT_USB4105-xx-A_16P_TopMnt_Horizontal
J2: Battery connector; PinHeader_1x02_P2.54mm_Vertical
L1: 1uH; L_0805_2012Metric
L2: 1.5uH; L_0805_2012Metric
L3: 2.2uH; L_0805_2012Metric
R1: 100K; R_0805_2012Metric
R2: 27.4k; R_0805_2012Metric
R3: 200k; R_0805_2012Metric
R4, R5, R9, R11: 10K; R_0805_2012Metric
R6, R7, R10: 10k; R_0805_2012Metric
R8: 260ohm; R_0805_2012Metric
R12: 900K; R_0805_2012Metric
U1: TPS61023DRLR; SOT563-ORI; MPN TPS61023DRLR
U2: TPS63021DSJR; DSJ14_2P85X1P58
U3: BQ25895RTW; Texas_RTW_WQFN-24-1EP_4x4mm_P0.5mm_EP2.7x2.7mm_ThermalVias
U4: TUSB320LAIRWBR; RWB0012A_TEX

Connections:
+5V_AUD: FB1.2; also elsewhere on the board
+5V_LCD: C6.1, FB1.1, R3.1, U1.6 (VOUT); also elsewhere on the board
/Power_Management/BAT: C14.1, J2.1, U3.13 (BAT), U3.14 (BAT)
/Power_Management/BQ_CE_N: R7.2, U3.9 (~CE)
/Power_Management/BTST: C11.1, U3.21 (BTST)
/Power_Management/CC1: J1.A5 (CC1), U4.1 (CC1)
/Power_Management/CC2: J1.B5 (CC2), U4.2 (CC2)
/Power_Management/DIH +: J1.A6 (D+), J1.B6 (D+), U3.2 (D+)
/Power_Management/DIH -: J1.A7 (D-), J1.B7 (D-), U3.3 (D-)
/Power_Management/PMID: C10.1, U3.23 (PMID)
/Power_Management/REGN: C15.1, R11.1, U3.22 (REGN)
/Power_Management/SW: C11.2, L3.1, U3.19 (SW), U3.20 (SW)
/Power_Management/SYS: C1.1, C2.1, C8.1, C9.1, C12.1, C13.1, L1.1, L3.2, U1.3 (VIN), U2.1 (VINA), U2.10 (VIN), U2.11 (VIN), U2.12 (EN), U2.13 (PS/SYNC), U3.15 (SYS), U3.16 (SYS)
/Power_Management/VBUS: C7.2, J1.A4 (VBUS), J1.A9 (VBUS), J1.B4 (VBUS), J1.B9 (VBUS), R12.1, U3.1 (VBUS)
BOOST_EN: R1.2, U1.2 (EN); also elsewhere on the board
BQ_INT: R4.2, U3.7 (~INT); also elsewhere on the board
DAC_DGND: C1.2, C2.2, C3.2, C4.2, C5.2, C6.2, C7.1, C8.2, C9.2, C10.2, C12.2, C13.2, C14.2, C15.2, C16.1, J1.A1 (GND), J1.A12 (GND), J1.B1 (GND), J1.B12 (GND), J1.SH (SHIELD), J2.2, R1.1, R2.2, R7.1, R8.1, R9.2, U1.4 (GND), U2.2 (GND), U2.15 (EPAD), U3.8 (OTG), U3.17 (PGND), U3.18 (PGND), U3.25 (PGND), U4.3 (PORT), U4.5 (ADDR), U4.10 (GND), U4.11 (EN_N); also elsewhere on the board
DAC_DVCC: C3.1, C4.1, C5.1, C16.2, R4.1, R5.1, R6.1, R10.2, U2.3 (FB), U2.4 (VOUT), U2.5 (VOUT), U4.12 (VDD); also elsewhere on the board
I2C_SCL: R5.2, U3.5 (SCL), U4.8 (SCL_OUT2); also elsewhere on the board
I2C_SDA: R6.2, U3.6 (SDA), U4.7 (SDA_OUT1); also elsewhere on the board
unnamed: L2.1, U2.6 (L2), U2.7 (L2)
unnamed: L2.2, U2.8 (L1), U2.9 (L1)
unnamed: R2.1, R3.2, U1.1 (FB)
unnamed: L1.2, U1.5 (SW)
unnamed: R10.1, U3.24 (DSEL)
unnamed: R8.2, U3.10 (ILIM)
unnamed: R9.1, R11.2, U3.11 (TS)
unnamed: R12.2, U4.4 (VBUS_DET)

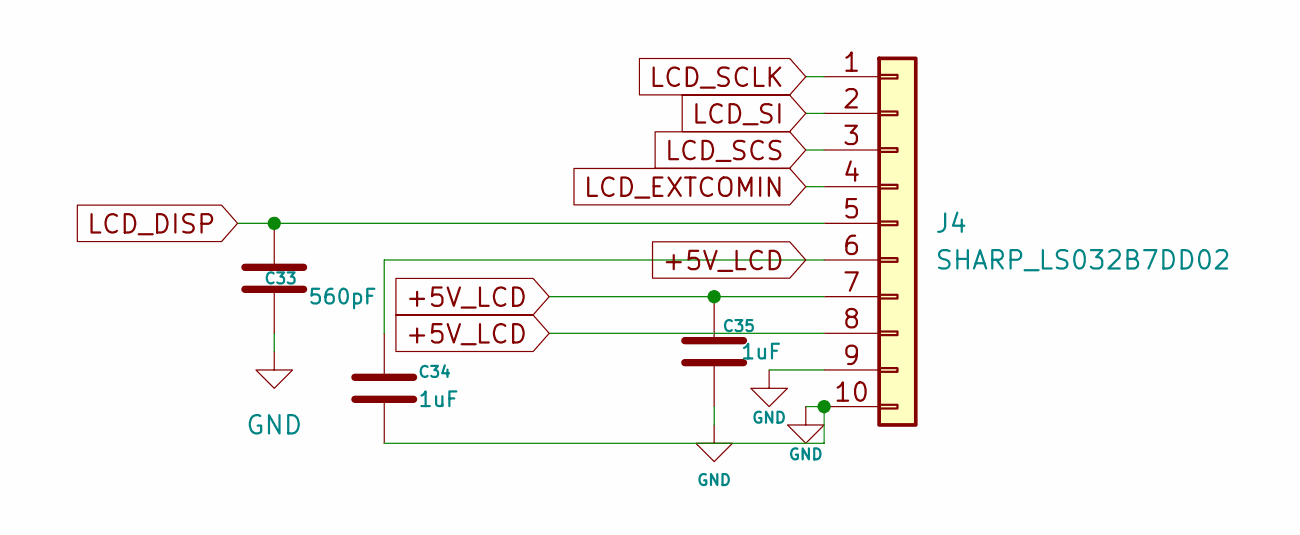
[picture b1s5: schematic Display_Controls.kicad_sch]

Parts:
C33: 560pF; C_0603_1608Metric
C34, C35: 1uF; C_0603_1608Metric
J4: SHARP_LS032B7DD02; HRS_FH34SRJ-10S-0.5SH_50_

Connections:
+5V_LCD: C34.1, C35.1, J4.6, J4.7, J4.8; also elsewhere on the board
DAC_DGND: C33.2, C34.2, C35.2, J4.9, J4.10; also elsewhere on the board
LCD_DISP: C33.1, J4.5; also elsewhere on the board
LCD_EXTCOMIN: J4.4; also elsewhere on the board
LCD_SCLK: J4.1; also elsewhere on the board
LCD_SCS: J4.3; also elsewhere on the board
LCD_SI: J4.2; also elsewhere on the board
